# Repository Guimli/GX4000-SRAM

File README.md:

# GX4000-SRAM

RAM replacement mod for GX4000 based on modern RAM. This mod can be used to replace the original RAM of the GX4000. And it is also possible to expand the GX4000's RAM to 128K.

This mod is inspired by the SRAM for C64 on https://github.com/jamarju/c64-sram

Video of the installation of this mod on the Twitch of RetroRedrum :

Approximate cost for one RAM mod (costs can be considerably reduced if you build several modules) :

- IS61C1024AL-12HLI : 3.28 €
- SN74HCT573PWR : 0.58 €
- SN74LVC1G08DBVR : 0.36 €
- SN74LVC1G32DBVR : 0.38 €
- R1 & R2 : 0.10 €
- C1 & C2 : 0.84 €
- PCB (minimum 5 + Shipping) : 14.95€
- IC10 & IC11 (Headers 20 pin) : 2.49€
- Round Pinheader (10x 1x40) : 8.19€

Total : 31,32€

I can sell you modules already assembled. But the shipping costs from France are prohibitive...

To enable the 128K mod, add a 10 kΩ resistor between pins 8 and 11 of IC8 (74HC4051).

And connect pin 91 of the ASIC to the dedicated CAS1 slot on the mod.

(See https://www.cpcwiki.eu/index.php/128k_on_GX-4000 for more information)

## BOM
| Quantity | Description | Part Number | Mouser | Notes |
|:--------:|:------------|-------------|---------|-------|
| 1        | SRAM 1Mbit pin 32 TSOP I-32 | IS61C1024AL-12HLI | [870-61C1024AL-12HLI](https://www.mouser.fr/ProductDetail/ISSI/IS61C1024AL-12HLI?qs=NHlAyh8rbXxX6sVqjKW4FQ%3D%3D) | |
| 1        | 74HCT573 pin 20 TSSOP | SN74HCT573PWR | [595-SN74HCT573PWR](https://www.mouser.fr/ProductDetail/Texas-Instruments/SN74HCT573PWR?qs=CCO124VRWrmt55RoEPLmzg%3D%3D) | |
| 1        | 74LVC1G32 pin 5 SOT-23-5 | SN74LVC1G32DBVR  | [595-SN74LVC1G32DBVR](https://www.mouser.fr/ProductDetail/Texas-Instruments/SN74LVC1G32DBVR?qs=3pnr37ZAbK%2F6ArGi%2FPb2Ng%3D%3D) | |
| 1        | 74LVC1G08 pin 5 SOT-23-5 | SN74LVC1G08DBVR  | [595-SN74LVC1G08DBVR](https://www.mouser.fr/ProductDetail/Texas-Instruments/SN74LVC1G08DBVR?qs=8yeEWhuAOtNjtL049wSCoQ%3D%3D) | |
| 2        | 100nf / 0.1uf Ceramic Capacitor 0805 Size | C0805C104K5RAC7411 | [80-C0805C104K5RACLR](https://www.mouser.fr/ProductDetail/KEMET/C0805C104K5RAC7411?qs=sGAEpiMZZMvsSlwiRhF8qqQ8hxcT1iMuvRkk9zDM%252BLQ%3D) | Any 100nf 0805 is fine |
| 1        | 47K Ohm resistor 0805 Size | CR0805-JW-473ELF  | [652-CR0805JW-473ELF](https://www.mouser.fr/ProductDetail/Bourns/CR0805-JW-473ELF?qs=sGAEpiMZZMvdGkrng054t%252BRNGJdg958R0YzgB9JoA2g%3D) | Any 47KΩ 0805 resistor is fine |
| 1        | 33 Ohm resistor 0805 Size | CR0805-JW-330ELF | [652-CR0805JW-330ELF ](https://www.mouser.fr/ProductDetail/Bourns/CR0805-JW-330ELF?qs=sGAEpiMZZMvdGkrng054t%252BRNGJdg958RR%252BUoE30LIPU%3D) | Any 33Ω 0805 resistor is fine |

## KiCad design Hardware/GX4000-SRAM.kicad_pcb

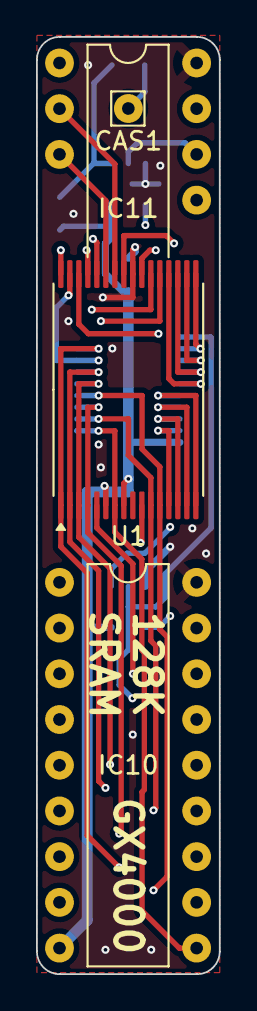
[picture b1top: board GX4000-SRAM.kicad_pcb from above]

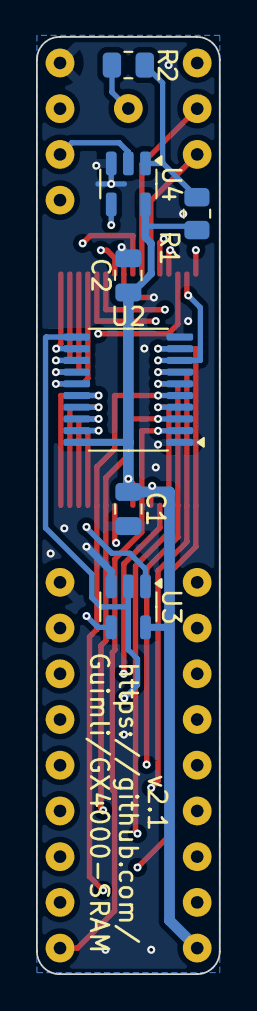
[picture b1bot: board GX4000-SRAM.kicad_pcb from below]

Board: 4 copper layers, 10.2 x 52.1 mm, 11 parts (7 on the bottom side), 34 nets.

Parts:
C1, C2: 100nF; C_0805_2012Metric
CAS1: Conn_01x01; Pin_D0.7mm_L6.5mm_W1.8mm_FlatFork
IC10, IC11: TMS4464; DIP-18_W7.62mm_LongPads
R1: 47k; R_0805_2012Metric
R2: 33; R_0805_2012Metric
U1: IS61C1024AL-12HLI; TSOP-I-32_11.8x8mm_P0.5mm
U2: SN74HCT573PWR; TSSOP-20_4.4x6.5mm_P0.65mm
U3: 74LVC1G32; SOT-23-5
U4: 74LVC1G08; SOT-23-5

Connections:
/A0: U1.20 (A0), U2.15 (Q4)
/A1: U1.19 (A1), U2.14 (Q5)
/A2: U1.18 (A2), U2.13 (Q6)
/A3: U1.17 (A3), U2.12 (Q7)
/A4: U1.16 (A4), U2.16 (Q3)
/A5: U1.15 (A5), U2.17 (Q2)
/A6: U1.14 (A6), U2.18 (Q1)
/A7: U1.13 (A7), U2.19 (Q0)
/D0: IC10.2 (DQ1), U1.21 (I/O0)
/D1: IC10.3 (DQ2), U1.22 (I/O1)
/D2: IC10.15 (DQ3), U1.23 (I/O2)
/D3: IC10.17 (DQ4), U1.25 (I/O3)
/D4: IC11.2 (DQ1), U1.26 (I/O4)
/D5: IC11.3 (DQ2), U1.27 (I/O5)
/D6: IC11.15 (DQ3), U1.28 (I/O6)
/D7: IC11.17 (DQ4), U1.29 (I/O7)
/MA0: IC10.14 (A0), U1.3 (A8), U2.6 (D4)
/MA1: IC10.13 (A1), U1.2 (A9), U2.7 (D5)
/MA2: IC10.12 (A2), U1.31 (A10), U2.8 (D6)
/MA3: IC10.11 (A3), U1.1 (A11), U2.9 (D7)
/MA4: IC10.8 (A4), U1.12 (A12), U2.5 (D3)
/MA5: IC10.7 (A5), U1.4 (A13), U2.4 (D2)
/MA6: IC10.6 (A6), U1.11 (A14), U2.3 (D1)
/MA7: IC10.10 (A7), U1.7 (A15), U2.2 (D0)
/~CAS0: IC10.16 (~CAS), IC11.16 (~CAS), U1.10 (A16), U4.2
/~CAS1: R1.2, R2.2, U4.1
/~OE: IC10.1 (~G), IC11.1 (~G), U1.32 (~OE)
/~RAS: IC10.5 (~RAS), U2.11 (Load), U3.2
/~WE: IC10.4 (~W), U1.5 (~WE)
GND: C1.2, C2.2, IC10.18 (GND), IC11.18 (GND), U1.24 (GND), U2.1 (OE), U2.10 (GND), U3.3 (GND), U4.3 (GND)
unnamed: CAS1.1, R2.1
unnamed: U1.30 (~CE1), U3.4
unnamed: U3.1, U4.4
VCC: C1.1, C2.1, IC10.9 (VCC), R1.1, U1.6 (CE2), U1.8 (VDD), U2.20 (VCC), U3.5 (VCC), U4.5 (VCC)

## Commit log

2022-11-08 Fixes the expacement between U10 and U11
2022-11-09 Release PCB
2023-02-19 v2.1
2025-01-27 Update Kicad version to 8
    - Update Kicad version format
    - Update Footprint
    - Add JLCPCB component reference
    - Add BOM in description
2025-01-27 Update README.md
    - Correct IS61C1024AL-12TLI to IS61C1024AL-12HLI
